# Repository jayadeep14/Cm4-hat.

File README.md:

# Custom Rpi Cm4 hat

i design a custom rpi cm4 hat for aome python based future projects like ai assistant, ai drone people finder,..like these ao ai based stuffs. 
for this life project , obviously i need money to make it real for my project. i even left space for expansion headers because future proofing or whatever. no idea how many late nights went into these projects.
# features

• rpi cm4 module

• Ethernet port

• usb and otg ports

• fuel gauge 

• battery connection 

• 5v booster

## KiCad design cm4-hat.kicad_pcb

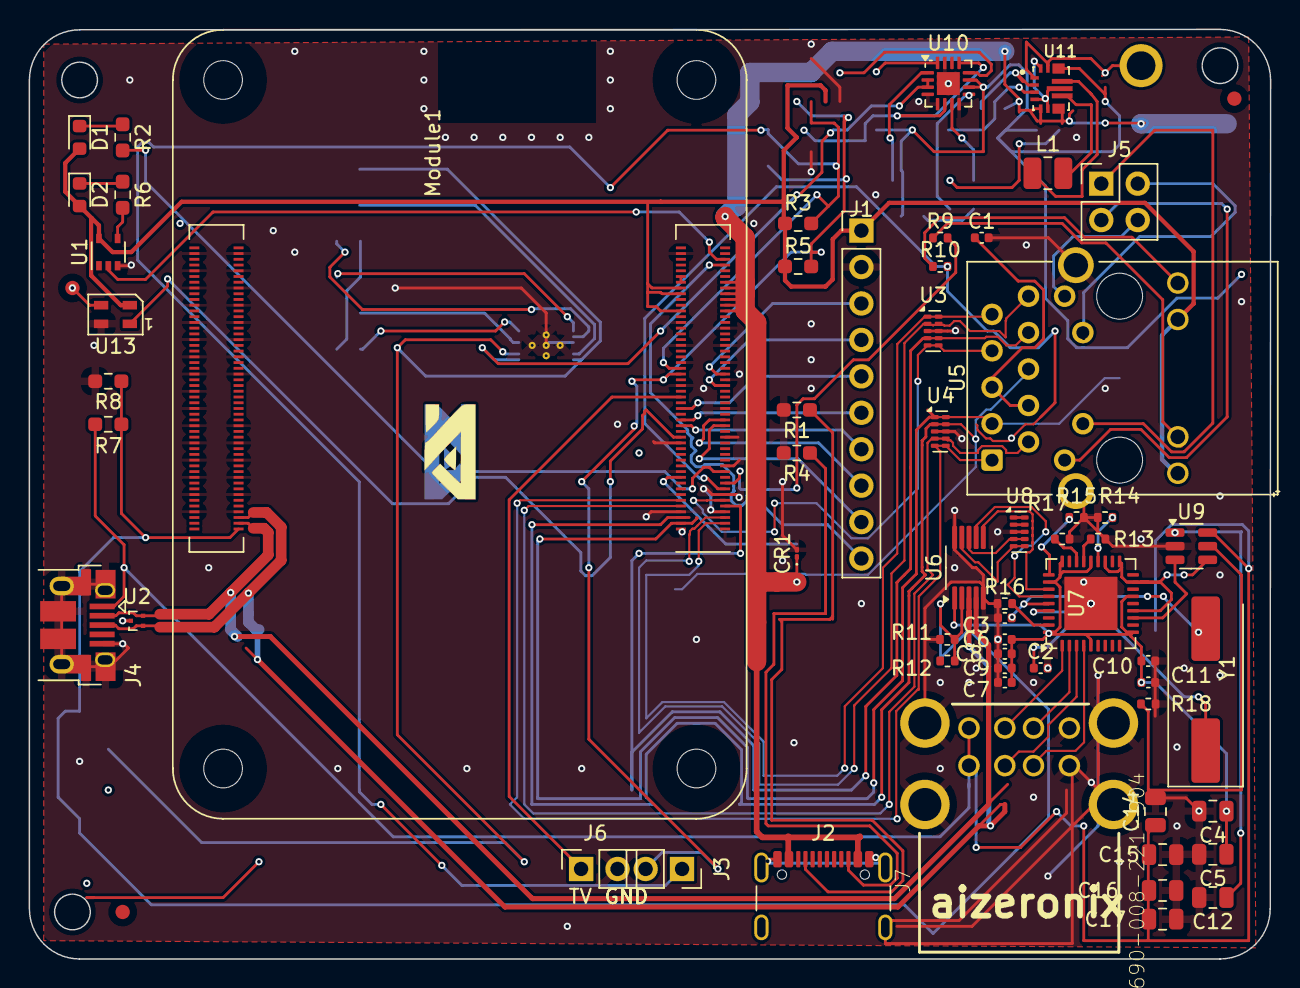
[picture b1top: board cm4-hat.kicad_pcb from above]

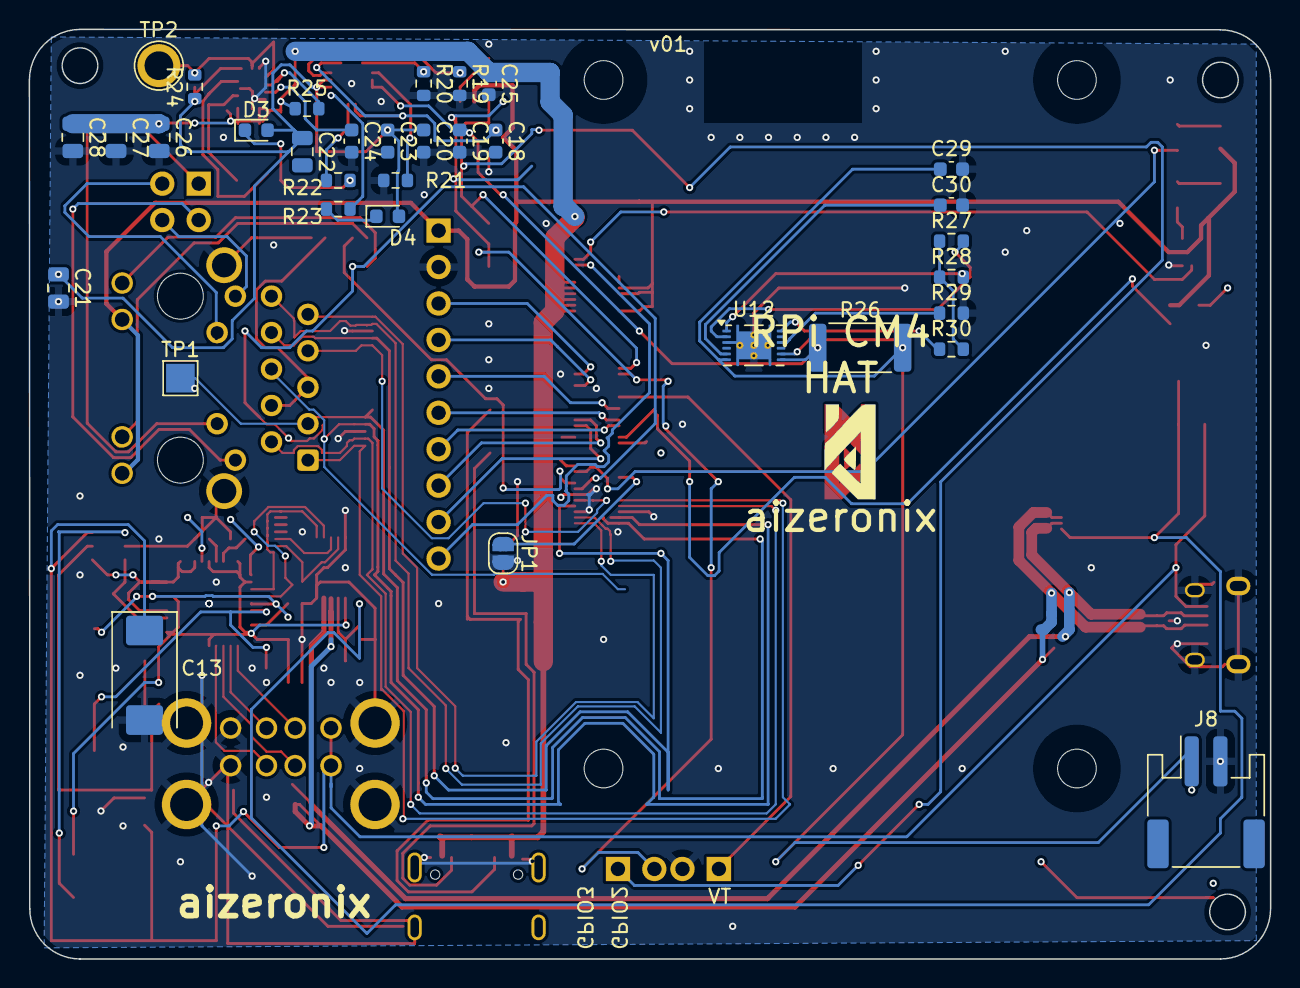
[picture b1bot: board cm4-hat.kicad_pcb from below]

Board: 2 copper layers, 86.5 x 64.8 mm, 94 parts (34 on the bottom side), 90 nets.

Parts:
C1, C6, C7, C8, C9, C10, C11: 100n; C_0402_1005Metric
C2, C3: 27pF; C_0402_1005Metric
C4, C5, C12, C14, C15, C16, C17: 10u; C_0805_2012Metric
C13: 100uF; CP_EIA-7343-31_Kemet-D
C18, C29: 1uF; C_0603_1608Metric
C19, C20: 4.7uF; C_0603_1608Metric
C21, C22: 10uF; C_0805_2012Metric
C23, C25: 10uF; C_0603_1608Metric
C24: 100nF; C_0603_1608Metric
C26, C27, C28: 22uF; C_0805_2012Metric
C30: 0.47uF; C_0603_1608Metric
CR1: SMBJ5.0A-TR; D_01005_0402Metric
D1: LED Green; LED_0603_1608Metric
D2: LED Red; LED_0603_1608Metric
D3: LED White; LED_0603_1608Metric
D4: LED Yellow; LED_0603_1608Metric
J1: DNP; PinHeader_1x10_P2.54mm_Vertical
J2: USB4105-GF-A; USB_C_Receptacle_GCT_USB4105-xx-A_16P_TopMnt_Horizontal
J3, J6: Conn_01x02_Pin; PinSocket_1x02_P2.54mm_Vertical
J4: USB_OTG; USB_Micro-B_EDAC_UCON00686
J5: THD-02-R; PinHeader_2x02_P2.54mm_Vertical
J7: 690-008-221-904; MOLEX_USB_67298-4090
J8: Battery In; JST_PH_S2B-PH-SM4-TB_1x02-1MP_P2.00mm_Horizontal
JP1: SolderJumper_2_Open; SolderJumper-2_P1.3mm_Open_RoundedPad1.0x1.5mm
L1: 1.5uH; L_1008_2520Metric
Module1: ComputeModule4-CM4; Raspberry-Pi-4-Compute-Module
R1, R4: 5.1k; R_0603_1608Metric_Pad0.98x0.95mm_HandSolder
R2, R6: 1k; R_0603_1608Metric_Pad0.98x0.95mm_HandSolder
R3, R5: DNP; R_0603_1608Metric_Pad0.98x0.95mm_HandSolder
R7, R8: 2.2K 1%; R_0603_1608Metric_Pad0.98x0.95mm_HandSolder
R9, R10: 470R; R_0402_1005Metric
R11, R12: 2.2K 1%; R_0402_1005Metric
R13, R14, R15, R17: 36K 1%; R_0402_1005Metric
R16: 12K 1%; R_0402_1005Metric
R18: 15K 1%; R_0402_1005Metric
R19: 3.3k; R_0603_1608Metric
R20: 1.8k; R_0603_1608Metric
R21, R24, R29, R30: 10k; R_0603_1608Metric
R22, R23: 1k; R_0603_1608Metric
R25: 100k; R_0603_1608Metric
R26: 0.010; R_2512_6332Metric
R27, R28: 5.1k; R_0603_1608Metric
TP1: TestPoint; TestPoint_Pad_2.0x2.0mm
TP2: TestPoint; TestPoint_Plated_Hole_D2.0mm
U1: 74LVC1G07SE-7; SOT-353_SC-70-5
U2: TPD2EUSB30; Texas_DRT-3
U3, U4, U8: TPD4EUSB30; USON-10_2.5x1.0mm_P0.5mm
U5: MagJack-A70-112-331N126; TRJG0926HENL
U6: FSUSB42MUX; MSOP-10_3x3mm_P0.5mm
U7: USB2514B-I/M2; QFN-36-1EP_6x6mm_P0.5mm_EP3.7x3.7mm
U9: AP22653W6; SOT-23-6
U10: BQ24075RGT; VQFN-16-1EP_3x3mm_P0.5mm_EP1.6x1.6mm
U11: TPS630701; VREG_TPS63070RNMR
U12: BQ27441-G1; Texas_S-PDSO-N12
U13: 4492; LED_SK6805_PLCC4_2.4x2.7mm_P1.3mm
Y1: 24MHz; Crystal_SMD_HC49-SD
_: LOGO; aizeronix
_#2: LOGO; aizeronix

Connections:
+1.8V: Module1.88 (+1.8v_(Output)), Module1.90 (+1.8v_(Output))
+3.3V: D1.2 (A), D2.2 (A), J1.1, Module1.78 (GPIO_VREF(1.8v/3.3v_Input)), Module1.84 (+3.3v_(Output)), Module1.86 (+3.3v_(Output)), R3.1, R5.1, U1.5 (VCC), U5.15 (LEDG_A), U5.17 (LEDY_A), U13.2 (VDD)
+3V3: R27.1, R28.1, R30.2
+5V: C25.1, C26.1, C27.1, C28.1, CR1.1, Module1.77 (+5v_(Input)), Module1.79 (+5v_(Input)), Module1.81 (+5v_(Input)), Module1.83 (+5v_(Input)), Module1.85 (+5v_(Input)), Module1.87 (+5v_(Input)), R25.1, U11.5 (FB)
+BATT: C29.1, J8.1, R26.2, U12.6 (BAT), U12.8 (SRP)
/CM4 GPIO/EEPROM_nWP: JP1.1 (A), Module1.20 (EEPROM_nWP)
/CM4 GPIO/ETH_LEDG: Module1.17 (Ethernet_nLED2(3.3v)), R9.2
/CM4 GPIO/ETH_LEDY: Module1.15 (Ethernet_nLED3(3.3v)), R10.2
/CM4 GPIO/GPIO2: J3.1, Module1.58 (GPIO2), R3.2
/CM4 GPIO/GPIO3: J3.2, Module1.56 (GPIO3), R5.2
/CM4 GPIO/GPIO5: Module1.34 (GPIO5), U13.1 (DIN)
/CM4 GPIO/GPIO7: J1.9, Module1.37 (GPIO7)
/CM4 GPIO/GPIO8: J1.8, Module1.39 (GPIO8)
/CM4 GPIO/GPIO9: J1.6, Module1.40 (GPIO9)
/CM4 GPIO/GPIO10: J1.5, Module1.44 (GPIO10)
/CM4 GPIO/GPIO11: J1.7, Module1.38 (GPIO11)
/CM4 GPIO/GPIO14: J1.3, Module1.55 (GPIO14)
/CM4 GPIO/GPIO15: J1.4, Module1.51 (GPIO15)
/CM4 GPIO/GPIO27: J6.1, Module1.48 (GPIO27)
/CM4 GPIO/TR0_TAP: J5.3, U5.11 (VC1)
/CM4 GPIO/TR1_TAP: J5.1, U5.12 (VC2)
/CM4 GPIO/TR2_TAP: J5.2, U5.13 (VC3)
/CM4 GPIO/TR3_TAP: J5.4, U5.14 (VC4)
/CM4 GPIO/TRD0_N: Module1.10 (Ethernet_Pair0_N), U4.4 (D2+), U4.7, U5.2 (TRD0-)
/CM4 GPIO/TRD0_P: Module1.12 (Ethernet_Pair0_P), U4.5 (D2-), U4.6, U5.1 (TRD0+)
/CM4 GPIO/TRD1_N: Module1.6 (Ethernet_Pair1_N), U4.2 (D1-), U4.9, U5.6 (TRD1-)
/CM4 GPIO/TRD1_P: Module1.4 (Ethernet_Pair1_P), TP1.1, U4.1 (D1+), U4.10, U5.3 (TRD1+)
/CM4 GPIO/TRD2_N: Module1.9 (Ethernet_Pair2_N), U3.4 (D2+), U3.7, U5.8 (TRD2-)
/CM4 GPIO/TRD2_P: Module1.11 (Ethernet_Pair2_P), U3.5 (D2-), U3.6, U5.7 (TRD2+)
/CM4 GPIO/TRD3_N: Module1.5 (Ethernet_Pair3_N), U3.2 (D1-), U3.9, U5.10 (TRD3-)
/CM4 GPIO/TRD3_P: U3.1 (D1+), U3.10, U5.9 (TRD3+)
/CM4 GPIO/nLED_Activity: Module1.21 (PI_nLED_Activity), R2.2
/CM4 GPIO/nPWR_LED: Module1.95 (nPI_LED_PWR), U1.2
/CM4 GPIO/nRPIBOOT: J1.10, Module1.93 (nRPIBOOT)
/CM4 High Speed/BATT_OUT: C19.1, R26.1, U10.2 (BAT), U10.3 (BAT), U12.7 (SRN)
/CM4 High Speed/CHG_OUT: C20.1, C21.1, C22.1, C23.1, D3.2 (A), D4.2 (A), R24.1, U10.10 (OUT), U10.11 (OUT)
/CM4 High Speed/L1: L1.1, U11.11 (L1)
/CM4 High Speed/L2: L1.2, U11.9 (L2)
/CM4 High Speed/USB2-HUB/+3.3v: C4.1, C5.1, C6.1, C7.1, C8.1, C9.1, C10.1, C11.1, U6.1 (VCC), U7.5 (VDDA33), U7.10 (VDDA33), U7.15 (VDD33), U7.23 (VDD33), U7.27 (VBUS_DET), U7.29 (VDDA33), U7.36 (VDDA33)
/CM4 High Speed/USB2-HUB/+5v: C12.1, U9.1 (IN)
/CM4 High Speed/USB2-HUB/HD1_N: J7.2 (D-`), U7.1 (USBDM_DN1/PRT_DIS_M1)
/CM4 High Speed/USB2-HUB/HD1_P: J7.3 (D+`), U7.2 (USBDP_DN1/PRT_DIS_P1)
/CM4 High Speed/USB2-HUB/HD2_N: J7.6 (D-), U7.3 (USBDM_DN2/PRT_DIS_M2)
/CM4 High Speed/USB2-HUB/HD2_P: J7.7 (D+), U7.4 (USBDP_DN2/PRT_DIS_P2)
/CM4 High Speed/USB2-HUB/PWR1: U7.12 (PRTPWR1/BC_EN1), U9.3 (EN)
/CM4 High Speed/USB2-HUB/USBD_N: U6.8 (HSD1_M), U8.4 (D2+), U8.7
/CM4 High Speed/USB2-HUB/USBD_P: U6.9 (HSD1_P), U8.5 (D2-), U8.6
/CM4 High Speed/USB2-HUB/USBH_N: U6.6 (HSD0_M), U7.30 (USBDM_UP)
/CM4 High Speed/USB2-HUB/USBH_P: U6.7 (HSD0_P), U7.31 (USBDP_UP)
/CM4 High Speed/USB2-HUB/VBUS: C13.1, C14.1, C15.1, C16.1, C17.1, J7.1 (VBUS`), J7.5 (VBUS), U9.6 (OUT)
/CM4 High Speed/USB2-HUB/nOCS1: U7.13 (OCS_N1), U7.17 (OCS_N2), U7.19 (OCS_N3), U7.21 (OCS_N4), U9.4 (nFault)
/CM4 High Speed/USB2_N: J4.2 (D-), Module1.103 (USB2_N), U2.2 (D-), U6.4 (D_N)
/CM4 High Speed/USB2_P: J4.3 (D+), Module1.105 (USB2_P), U2.1 (D+), U6.3 (D_P)
/CM4 High Speed/USB_OTG_ID: Module1.101 (USB_OTG_ID), R7.2, R8.1, R11.1, R12.2, U6.2 (SEL)
/CM4 High Speed/~CHG: R23.2, U10.9 (~CHG)
/CM4 High Speed/~PGOOD: R22.2, U10.7 (~PGOOD)
GND: C1.2, C2.2, C3.2, C4.2, C5.2, C6.2, C7.2, C8.2, C9.2, C10.2, C11.2, C12.2, C13.2, C14.2, C15.2, C16.2, C17.2, C18.2, C19.2, C20.2, C21.2, C23.2, C24.2, C25.2, C26.2, C27.2, C28.2, C29.2, C30.2, CR1.2, J1.2, J4.5 (GND), J4.6 (Shield), J6.2, J7.4 (GND`), J7.8 (GND), J7.MT1, J7.MT2, J7.MT3, J7.MT4, J8.2, JP1.2 (B), Module1.1 (GND), Module1.2 (GND), Module1.7 (GND), Module1.8 (GND), Module1.13 (GND), Module1.14 (GND), Module1.22 (GND), Module1.23 (GND), Module1.32 (GND), Module1.33 (GND), Module1.42 (GND), Module1.43 (GND), Module1.52 (GND), Module1.53 (GND), Module1.59 (GND), Module1.60 (GND), Module1.65 (GND), Module1.66 (GND), Module1.71 (GND), Module1.74 (GND), Module1.98 (GND), Module1.107 (GND), Module1.108 (GND), Module1.113 (GND), Module1.114 (GND), Module1.119 (GND), Module1.120 (GND), Module1.125 (GND), Module1.126 (GND), Module1.131 (GND), Module1.132 (GND), Module1.137 (GND), Module1.138 (GND), Module1.144 (GND), Module1.150 (GND), Module1.155 (GND), Module1.156 (GND), Module1.161 (GND), Module1.162 (GND), Module1.167 (GND), Module1.168 (GND), Module1.173 (GND), Module1.174 (GND), Module1.179 (GND), Module1.180 (GND), Module1.185 (GND), Module1.186 (GND), Module1.191 (GND), Module1.192 (GND), Module1.197 (GND), Module1.198 (GND), R1.2, R4.2, R8.2, R11.2, R13.2, R14.2, R15.2, R16.1, R17.2, R18.2, R19.2, R20.2, R21.2, R29.2, U1.3 (GND), U2.3 (GND), U3.3 (GND), U3.8 (GND), U4.3 (GND), U4.8 (GND), U5.19 (SHIELD), U5.20 (SHIELD), U6.5 (GND), U6.10 (nOE), U7.37 (VSS), U8.3 (GND), U8.8 (GND), U9.2 (GND), U10.4 (~CE), U10.5 (EN2), U10.8 (VSS), U10.15 (SYSOFF), U10.17 (VSS), U11.4 (GND), U11.6 (FB2), U11.10 (PGND), U11.15 (VSEL), U12.3 (V_{SS}), U12.13 (PAD), U13.4 (GND)
unnamed: C1.1, U5.4 (CT), U5.5 (CT)
unnamed: D1.1 (K), R2.1
unnamed: D2.1 (K), R6.1
unnamed: D3.1 (K), R22.1
unnamed: D4.1 (K), R23.1
unnamed: J2.A5 (CC1), R1.1
unnamed: J2.B5 (CC2), R4.1
unnamed: J4.1 (VBUS), R7.1
unnamed: R6.2, U1.4
unnamed: R9.1, U5.16 (LEDG_K)
unnamed: R10.1, U5.18 (LEDY_K)
unnamed: R17.1, U7.25 (HS_IND/CFG_SEL1)
unnamed: R16.2, U7.35 (RBIAS)
unnamed: R13.1, U7.24 (SCL/SMBCLK/CFG_SEL0)
unnamed: R14.1, U7.22 (SDA/SMBDATA/NON_REM1)
unnamed: R15.1, U7.28 (SUSP_IND/LOCAL_PWR/NON_REM0)
unnamed: C2.1, U7.33 (XTALIN/CLKIN), Y1.1
unnamed: C3.1, U7.32 (XTALOUT), Y1.2
unnamed: U8.1 (D1+), U8.10
unnamed: U8.2 (D1-), U8.9
unnamed: R18.1, U9.5 (ILIM)
unnamed: R19.1, U10.12 (ILIM)
unnamed: R20.1, U10.16 (ISET)
unnamed: R21.1, U10.1 (TS)
unnamed: R24.2, TP2.1, U11.1 (PS/SYNC), U11.14 (EN)
unnamed: R25.2, U11.2 (PG)
unnamed: C24.1, U11.3 (VAUX)
unnamed: R29.1, U12.10 (BIN)
unnamed: R30.1, U12.12 (GPOUT)
unnamed: R27.2, U12.2 (SCL)
unnamed: R28.2, U12.1 (SDA)
unnamed: C30.1, U12.5 (V_{DD})
VBUS: C18.1, U10.6 (EN1), U10.13 (IN)

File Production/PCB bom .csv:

Designator,Value,Package,Mid X,Mid Y,Rotation,Layer
C13,100uF,CP_EIA-7343-31_Kemet-D,-195,-123.5,-90,bottom
C18,1uF,C_0603_1608Metric,-170.5225,-86.26,-90,bottom
C19,4.7uF,C_0603_1608Metric,-173.0325,-86.26,-90,bottom
C20,4.7uF,C_0603_1608Metric,-175.5425,-86.26,-90,bottom
C21,10uF,C_0805_2012Metric,-201,-96.5,-90,bottom
C22,10uF,C_0805_2012Metric,-184,-87,-90,bottom
C23,10uF,C_0603_1608Metric,-178.0525,-86.26,-90,bottom
C24,100nF,C_0603_1608Metric,-180.5625,-86.26,-90,bottom
C25,10uF,C_0603_1608Metric,-171,-82.25,-90,bottom
C26,22uF,C_0805_2012Metric,-193.98,-86,-90,bottom
C27,22uF,C_0805_2012Metric,-196.99,-86,-90,bottom
C28,22uF,C_0805_2012Metric,-200,-86,-90,bottom
C29,1uF,C_0603_1608Metric,-138.75,-88.215,180,bottom
C30,0.47uF,C_0603_1608Metric,-138.75,-90.725,180,bottom
D3,LED White,LED_0603_1608Metric,-187.2125,-85.5,180,bottom
D4,LED Yellow,LED_0603_1608Metric,-178.0525,-91.5,180,bottom
J8,Battery In,JST_PH_S2B-PH-SM4-TB_1x02-1MP_P2.00mm_Horizontal,-121,-132.35,180,bottom
R19,3.3k,R_0603_1608Metric,-173.0325,-82.25,-90,bottom
R20,1.8k,R_0603_1608Metric,-175.5425,-82.25,-90,bottom
R21,10k,R_0603_1608Metric,-177.5,-89,0,bottom
R22,1k,R_0603_1608Metric,-181.5,-89,0,bottom
R23,1k,R_0603_1608Metric,-181.5,-91,180,bottom
R24,10k,R_0603_1608Metric,-191.5,-82.475,90,bottom
R25,100k,R_0603_1608Metric,-183.675,-84,180,bottom
R26,0.01,R_2512_6332Metric,-145.11,-100.665,180,bottom
R27,5.1k,R_0603_1608Metric,-138.75,-93.235,180,bottom
R28,5.1k,R_0603_1608Metric,-138.75,-95.745,180,bottom
R29,10k,R_0603_1608Metric,-138.75,-98.255,180,bottom
R30,10k,R_0603_1608Metric,-138.75,-100.765,180,bottom
U12,BQ27441-G1,Texas_S-PDSO-N12,-152.525,-100.5,180,bottom
,,,119.5,-96.5,0,top
C1,100n,C_0402_1005Metric,182.89,-93,0,top
C2,27pF,C_0402_1005Metric,187,-123,0,top
C3,27pF,C_0402_1005Metric,184.5,-119.5,180,top
C4,10u,C_0805_2012Metric,199,-132.97,180,top
C5,10u,C_0805_2012Metric,199,-135.98,180,top
C6,100n,C_0402_1005Metric,184.5,-121,180,top
C7,100n,C_0402_1005Metric,184.5,-124,180,top
C8,100n,C_0402_1005Metric,184.5,-122,180,top
C9,100n,C_0402_1005Metric,184.5,-123,180,top
C10,100n,C_0402_1005Metric,194.5,-122.5,0,top
C11,100n,C_0402_1005Metric,194.5,-124,0,top
C12,10u,C_0805_2012Metric,199,-138.99,180,top
C14,10u,C_0805_2012Metric,195,-133,90,top
C15,10u,C_0805_2012Metric,195.5,-136,0,top
C16,10u,C_0805_2012Metric,195.5,-138.5,0,top
C17,10u,C_0805_2012Metric,195.5,-140.5,0,top
CR1,SMBJ5.0A-TR,D_01005_0402Metric,170,-115,90,top
D1,LED Green,LED_0603_1608Metric,120,-86,-90,top
D2,LED Red,LED_0603_1608Metric,120,-90,-90,top
J1,DNP,PinHeader_1x10_P2.54mm_Vertical,174.5,-92.5,0,top
J2,USB4105-GF-A,USB_C_Receptacle_GCT_USB4105-xx-A_16P_TopMnt_Horizontal,171.85,-140,0,top
J3,Conn_01x02_Pin,PinSocket_1x02_P2.54mm_Vertical,162,-137,-90,top
J4,USB_OTG,USB_Micro-B_EDAC_UCON00686,118.75,-120,-90,top
J5,THD-02-R,PinHeader_2x02_P2.54mm_Vertical,191.225,-89.225,0,top
J6,Conn_01x02_Pin,PinSocket_1x02_P2.54mm_Vertical,154.96,-137,90,top
J7,690-008-221-904,MOLEX_USB_67298-4090,185.5,-132.5075,0,top
L1,1.5uH,L_1008_2520Metric,187.5,-88.5,0,top
Module1,ComputeModule4-CM4,Raspberry-Pi-4-Compute-Module,163,-82,180,top
R1,5.1k,R_0603_1608Metric_Pad0.98x0.95mm_HandSolder,170,-105,180,top
R2,1k,R_0603_1608Metric_Pad0.98x0.95mm_HandSolder,123,-86,-90,top
R3,DNP,R_0603_1608Metric_Pad0.98x0.95mm_HandSolder,170.0875,-92,0,top
R4,5.1k,R_0603_1608Metric_Pad0.98x0.95mm_HandSolder,170,-108,180,top
R5,DNP,R_0603_1608Metric_Pad0.98x0.95mm_HandSolder,170.0875,-95,0,top
R6,1k,R_0603_1608Metric_Pad0.98x0.95mm_HandSolder,123,-90,-90,top
R7,2.2K 1%,R_0603_1608Metric_Pad0.98x0.95mm_HandSolder,122,-106,0,top
R8,2.2K 1%,R_0603_1608Metric_Pad0.98x0.95mm_HandSolder,122,-103,180,top
R9,470R,R_0402_1005Metric,180,-93.01,0,top
R10,470R,R_0402_1005Metric,180,-95,0,top
R11,2.2K 1%,R_0402_1005Metric,180.49,-121,180,top
R12,2.2K 1%,R_0402_1005Metric,180.5,-122.5,0,top
R13,36K 1%,R_0402_1005Metric,191,-114,0,top
R14,36K 1%,R_0402_1005Metric,191.49,-112.5,180,top
R15,36K 1%,R_0402_1005Metric,189.5,-112.5,0,top
R16,12K 1%,R_0402_1005Metric,184.5,-118.5,0,top
R17,36K 1%,R_0402_1005Metric,188.5,-114,0,top
R18,15K 1%,R_0402_1005Metric,194.5,-125.5,0,top
REF**,Fiducial_1mm_Mask2mm,Fiducial_1mm_Mask2mm,123,-140,0,top
REF**,Fiducial_1mm_Mask2mm,Fiducial_1mm_Mask2mm,200.5,-83.3,0,top
U1,74LVC1G07SE-7,SOT-353_SC-70-5,122,-94,90,top
U2,TPD2EUSB30,Texas_DRT-3,124,-119.7,90,top
U3,TPD4EUSB30,USON-10_2.5x1.0mm_P0.5mm,179.5,-99.5,0,top
U4,TPD4EUSB30,USON-10_2.5x1.0mm_P0.5mm,180,-106.5,0,top
U5,MagJack-A70-112-331N126,TRJG0926HENL,192.5,-102.785,90,top
U6,FSUSB42MUX,MSOP-10_3x3mm_P0.5mm,182,-116,90,top
U7,USB2514B-I/M2,QFN-36-1EP_6x6mm_P0.5mm_EP3.7x3.7mm,190.5,-118.5,90,top
U8,TPD4EUSB30,USON-10_2.5x1.0mm_P0.5mm,185.5,-113.5,0,top
U9,AP22653W6,SOT-23-6,197.5,-114.5,0,top
U10,BQ24075RGT,VQFN-16-1EP_3x3mm_P0.5mm_EP1.6x1.6mm,180.5625,-82.25,0,top
U11,TPS630701,VREG_TPS63070RNMR,187.725,-82.6,0,top
U13,4492,LED_SK6805_PLCC4_2.4x2.7mm_P1.3mm,122.5,-98.35,180,top
Y1,24MHz,Crystal_SMD_HC49-SD,198.5,-124.5,90,top

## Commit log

2025-12-01 Rename gerbers.zip to Production/gerbers.zip
